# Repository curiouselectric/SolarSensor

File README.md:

# Solar Sensor
A DIY solar irradiance sensor.

Here are the design files (hardware, PCB and firmware) for a relatively low cost solar irradaince sneesor (called a pyranometer).

[Information relating to the design choices for this unit is available in a blog post here](https://www.re-innovation.co.uk/docs/low-cost-diy-solar-irradiance-sensor-for-pv-system-monitoring/).

This pyranometer is design to measure solar irradiance in Watts per meter squared. This is useful for monitoring systems for solar photovoltaic panels. It can also be used as an indicator value for light levels in many systems.

The main things to note with this design are:

* It does not apply any corrections/filtes for human eye parameters (whcih Lux sensors use, typically for photography or dimming algorithms)
* It does not apply any corrections/filters for plant growing characteristics (typically called PAR  - [Photosynthetically active radiation](https://en.wikipedia.org/wiki/Photosynthetically_active_radiation)

The main issue with this design is the calibration of the sensor data to its actual real-world data. I have attempted to give sensible conversion factors for the sensors used, but calibration for each exact set up with 
calibrated measurement equipment is potentially needed, depending upon you application.

If you are looking for relative changes in irradiance then this sensor is perfectly suitable. 

# Overview
This unit reads irradiance from a photo diode sensor (like a P-N junction in a typical solar photovoltaic cell) every 100mS or so. 

The sensor uses an accurate 16 bit Analog to Digital converter (ADC) (rather than the 10 bit resolution on-board the micrcontorller). This allows for much finer montitoring of the very small current from the solar sensor. As the sensor will 'max out' well below typicaly outdoor irradiance levels, then we use a 6mm PTFE diffuse to attenuate the irradiance signal. This was caclualted from trial and error, but allows up to 2000W/m² to be measured.

There is also a temperature sensor on-board to adjust readings for the sensor temperature. 

It averages those values over different sampling periods of 1, 10, 60 (1 min), 600 (10 min), 3600 (1 hour) seconds. It has an ATMega328 microcontroller onboard for measuring the sensors, processing commands and returnign serial data. A simple serial interface has been implemented (at max 57600 baud) to service requests from another device (such as a data logger or monitoring system). The serial requests can also have CRC for error checking.

I originally designed this to interface to an ESP32 data logger, which sleeps most of the time. The ESP32 wakes up, gets the data it needs, then goes back to sleep, knowing the solar sensor is always monitoring.

It was designed as a relatively simple interface to remove the need for monitoring irradiance data and averaging it. 
There are other dvices in this range, [including a wind sensor](https://www.curiouselectric.co.uk/collections/environment/products/wind-sensor-interface).

## Irradiance Measurements

The unit stores average irradiance values from the sensor for 1 second, 10 second, 1 min, 10 min and 1 hour values. It also records the maximum and minimum irradiance.

The unit converts the tiny current from the solar PV cell within a photodiode into a "Watts per meter squared" value using a y=mx+c linear conversion, where y is the irradiance value and x is the ADC reading from the photo diode sensor circuitry. m and c are stored in EEPROM and have default values of m=1 and c=0. These are floats and can be changed as required through the serial interface. Any updated values are stored in EEPROM. The output will not go negative - it will round out at 0.

The photodiode used within the prototype is the [SFH203 from OSRAM](https://look.ams-osram.com/m/67e1a90044b03ee9/original/SFH-203.pdf). This has an output repsonse between 400-1100nm with a sensitive area of 1mm² giving a whopping 80uA of photocurrent!

## Temperature Measurements

Temperature near to the board inside the unit is measured using a surface mounted LM75 I2C temperature sensor. This will give an approximate temperature of the sensor. This sensor is accurate to 0.5C. 
Temperature compensation can be applied by updating the config file within the fireware. If the "APPLY_TEMP_COMP" flag is set to "true" then the "TEMP_COMP_VAL" is applied at the real temperature compare to the "RATED_TEMP". Typically the rated temperature is 25C and comes from the [data sheet](https://look.ams-osram.com/m/67e1a90044b03ee9/original/SFH-203.pdf). For the SFH203 the "TEMP_COMP_VAL" is 0.18 %/K and the "RATED_TEMP" is 25C

So an example would be measuring 500 W/m² but the temperature sensor reads 50C.
The rated temperature is 25C, so we need to apply a compensation of (50 - 25) * 0.18 % = 4.5%, so the sensor will be reading 4.5% under the real value (as output is inversly affected by temperature), So the actual irradiance is 500 + (500*0.045) = 522.5 W/m². Not a huge difference, but this might be important.

You can also remove the temperature compensation and record the irradiance and temperature seperately and apply the compensation later.

# Operation

There are two mode of operation, depending upon your use case:

## Response Mode

In this mode then the unit responds to serial requests made. You ask the sensor for data and this is returned. It never sends anything unless asked. 

## Broadcast Mode

In this mode then the unit regularly sends data via the serial connunication. It will send the averaged data for (0) 1 second, (1) 10 second, (2) 1 min, (3) 10 min and (4) 1 hour averaged data. If this is set to (5) then the unit does not send any data. The send mdoe is stored in EEPROM, so it will start sending data again even if power is lost.

Boradcast mode works well if the logger is always listening and you only have one sensor in range. If more than one sensor is in range then the data will clash and potentially cause issues, in which case use Response mode.

The two modes work together - you can have the unit sending regular data and also responding to requests.

It runs on an ATMega328 running at 8MHz with selectable baud serial (up to 57600). It comes pre-programmed, but code can be uploaded via the Arduino IDE, using the MiniCore board add-on. See firmware for more details.

# Hardware

The PCB was designed in KiCAD and is available here. A small PCB has been designed.
There is one reset switch, one user input switch and one LED output.

## Board ID Number

Each unit can have a unique ID (using a solder pad for 0-7 values), so multiple units can be added to a serial bus, if needed. The defalt is 0.

## PCB User Switch and User LED

There is one user switch and one user LED on the unit.

The LED will show a regular flash every 5 seconds. This will briefly flash once every 5 seconds if the unit is in 'Response' mode. The LED will briefyl flash twice every 5 seconds if the unit is in 'Broadcast' mode. Data will be sent at the broadcast rate.

The LED will also flash whenever data is sent of the serial port. The LED will go on before data sent and then off after data is sent.

Pressing the user switch for >0.5 seconds and then releasing will result in a switch press. 

A switch press will increment the "mode" from 0-1-2-3-4-5 then back to 0. 

The unit will flash after a button press to indicate the broadcast mode (so 0 flashes if the value is 0, 1 flash if the value is 1 etc). 

If this is set to 5 then the unit works in 'Response' mode. 

If this is set to 0-4 then the unit is in 'Broadcast' mode and will send the data at the relevant interval (0 = 1s, 1 = 10s, 2 = 1 min, 3 = 10 min and 4 = 1 hour). 

The mode can also be set with a serial request, using the "Set the unit to broadcast:" method (see below).

# Firmware
This uses an ATMega328 running at 8MHz with 3.3v or 5V supply.

## Initial bootloader installation:
You should not need to do this, as the unit should come with this already installed. This is just for information.

To upload a bootloader it then MiniCore is used:

Install MiniCore from here: https://github.com/MCUdude/MiniCore

Install the bootloader using an Arduino as an ISP. https://www.arduino.cc/en/Tutorial/BuiltInExamples/ArduinoISP

Wire up your arduino and an ISP 3x2 header pin onto the wind sensor PCB.

Choose the "ATMega328" option with the "External 8MHz Oscillator" set.

You can then use the 'Burn Bootloader' option within 'Tools' in the Arduino IDE. This will install the Minicore bootloader.

## Program via Arduino IDE

To program it then MiniCore is used:

Install MiniCore from here: https://github.com/MCUdude/MiniCore

Add to preferences and then board manager.

You can then upload code by choosing the "ATMega328" option with the "External 8MHz Oscillator" set.

# Serial Data and Commands

It returns the average values and information when requested on serial port.

At all other times then the unit is asleep.

This unit is called the Solar Sensor, so I used "SS" as its simple serial name.

## Irradiance data:
REQUEST: “aaI0SSA4#”  ("aaI0SSA4?41#" with CRC)  Where 0 is an ID from 0-7 set by solder on PCB. 4 is the averaging period (0=1s, 1=10s, 2 = 60s, 3 = 600s, 4=3600s)  

RETURNED: "aaI0SSA1:28.5:28.6:28.5:18.0#" 

where the first number (between semi-colons) is the average, 2nd number is the Maximum (until a reset is done), 3rd number is the Minimum and 4th number is the temperature.

Temperature has a resolution of 0.5 C (18.0C in this example).

Response will include the averaging number (1 in this example).
                                      
## Irradiance data minimum:

REQUEST: “aaI0SSMN#” ("aaI0SSMN?dc#" with CRC) - does not matter what averaging period. min/max are just the min/max seen.

RETURNED: "aaI0SSMN:27.9#" where the number after semi-colon is the minimum. (+CRC if requested)
                                      
## Irradiance data maximum:

REQUEST: “aaI0SSMX#”  ("aaI0SSMX?be#" with CRC) - does not matter what averaging period. min/max are just the min/max seen.

RETURNED: "aaI0SSMX:28.9#" where the number after semi-colon is the maximum. (+CRC if requested)

## Reset the min/max:

REQUEST:   “aaI0RESET#” ("aaI0RESET?d9#" with CRC) this will Reset Min & Max.  

RETURNED:  Nothing

This command will reset the min/max. Min and max will be stored until this reset command is issued.

## What is Irradiance Sensor conversion?: 

REQUEST:  "aaI0SSCON#"    Ask for the stored irradiance conversion values

RETURNED: "aaI0SSCONm10.00c0.00#"  With the numbers after m and c being the conversion values (+CRC if requested).
                                      
## Set the Irradiance Sensor conversion:      

REQUEST:  "aaI0SSSETm123.4c567.89#"    SET the stored irradiance conversion values
  
RETURNED: "aaI0SSSETm123.4c567.89#"     With the numbers after m and c being the conversion values

Note: Request: "aaI0SSSETm1c0#" or "aaI0SSSETm1c0?34#" with CRC to set m= 1 and c=0. This is useful for initial testing.

## What is Temperature conversion?: 

REQUEST:  "aaI0SSTCON#"    Ask for the stored conversion values

RETURNED: "aaI0SSTCONp0.18r25.0#"  With the numbers after p being the percentage adjustment and r being the reated temperature (in C) (+CRC if requested).
                                      
## Set the Temperature conversion:      

REQUEST:  "aaI0SSTCONp0.18r25.0#"    SET the stored conversion values
  
RETURNED: "aaI0SSTCONp0.18r25.0#"     With the numbers after m and c being the conversion values

## Switch on/off Temperature conversion: 

REQUEST:  "aaI0SSTCONON#"  to set temperature conversion ON. REQUEST:  "aaI0SSTCONOFF#" to set temperature conversion OFF

RETURNED: "aaI0SSTCONON#" or "aaI0SSTCONOFF#" (+CRC if requested).
                                      
## Set the unit to broadcast:  
REQUEST: "aaI0SEND?#" where ? is an int (0)= 1s data, (1)= 10s data, (2)= 60s/1 min data, (3)= 600s/10 min data, (4)= 3600s/1hr data, (5)= NO data 

RETURNED: "aaI0SENDOK#" + CRC if requested

You can also set the unit to broadcast using the user switch. Press the button for around 0.5s or more then release. This will go through the boradcast modes from 0-1-2-3-4-5 then back round to 0. The LED will flash the number of times for the setting (so send = 0 the unit will not flash, but data will appear within 1 second!).

If the unit is in broadcast mode then the minimum and maximum wind speeds and the wind vane data are all reset each time period.

## What is baud rate?:                 
REQUEST: "aaI0BD#" ("aaI0BD?dc#" with CRC for device ID 0 or "aaI1BD?b7#" for device ID 1)

RETURNED: "aaBD9600#"  // Where 9600 is the baud rate + CRC if requested
                                      
## Set Baud Rate:                      
REQUEST: "aaI0STBD*#"  Where * is (0)1200, (1)2400, (2)9600, (3)57600, (4)115200

RETURNED: "aaBD9600#"   // Where 9600 is the baud rate + CRC if requested

## What is ID?:                        
Mentioned at start up of unit - it is solder-programmed... cannot be changed in code.

ID selection is by using a blob of solder to connect together some pads labelled A0, A1 and A2. The default is for no pads to be soldered and the ID is 0. This means the unit will respond to "I0" as the ID.

To change the ID to another number from 0-7 then we can solder the different connection pads to create a binay number. The connections are:

A0     |A1     |A2     | ID
-------|-------|-------|----
NC     |NC     |NC     | 0
Solder |NC     |NC     | 1
NC     |Solder |NC     | 2
Solder |Solder |NC     | 3
NC     |NC     |Solder | 4
Solder |NC     |Solder | 5
NC     |Solder |Solder | 6
Solder |Solder |Solder | 7

## Serial 'Button' press

The command "aaI0BUTTON" + CRC + "#" will act just like a button press. This is for control via a data logger serial port without access to the physical switch.
e.g. This is "aaI1BUTTON?f4#" including CRC for device ID 1.

## Add CRC check:           
Within the config of the firmware a CRC (Cyclic Redundancy Check) can be added to the data (or not!).

Set this true using the flag in the config.h file:

  #define ADD_CRC_CHECK     true    // Use this to add CRC check to incomming and outgoing messages

This uses the CRC routines from Rob Tillaart, available here: https://github.com/RobTillaart/CRC

A 'crc8' is perfromed on the data and a 2 byte CRC code is added to all replys (and expected on all enquiries). This is added between a ? and # symbol.

If no CRC then the end char is a #.

For example: aaI0RESET?d9# has the CRC check d9 added to the reset request.

Remember: Capitalisation will affect the results: D is not the same as d!

You can use this online calculator to check your CRC: https://crccalc.com/ 

**The type of CRC is CRC-8/SMBUS.**

## Failure codes:

If data is not that length or does not have 'aa' and '#' at start/end then return with send "aaFAIL**#" error code. All will have CRC on these codes, if requested.

## Analog Output

There is an analog output on the device which will always output a voltage which is proportional to the irradiance level. This is useful if you just want to see the data on a multimeter or some panel meter.

The unit is set with a maxinmum irradiance of 2000W/m². This will give the maximum output from the analog output (which will be Vcc (the supply voltage)). At an irradiance of 1000W/m² then the output will be Vcc/2.

This means we need a relatively stable and accurate power supply to give stable and accurate output.

Note: 
* Only have 256 levels for the analog output.
* Need to know Vcc to get absolute value
* Can output up to MAX_IRRADIANCE W/m2 MAX, which is set in the firmware to 2000W/m²
  
Example: So 1000 W/m2 = 256*1000/MAX_IRRADIANCE = PWM Value 128 => Vcc/ 2 (for MAX_IRRADIANCE = 2000 W/m2)
  
Example: So 100 W/m2 = 256*100/MAX_IRRADIANCE = PWM Value 12.8 (or 13 in discrete levels) => Vcc/20 (for MAX_IRRADIANCE = 2000 W/m2)

The resolution of the output is Vcc/256, so for 5V Vcc this is  0.01953V or 19.5mV

A reading of 1000W would be PWM of 128 which gives output of 2.5V

A reading of 100W would should give PWM of 12.8 (so output voltage should be 0.25V) BUT 12.8 is converted to 13 as an INT (rounding up)

So output is actually 0.2539V. Basically there is a 'step' of 19.5mV (at Vcc = 5V) so data will be 'stepped'

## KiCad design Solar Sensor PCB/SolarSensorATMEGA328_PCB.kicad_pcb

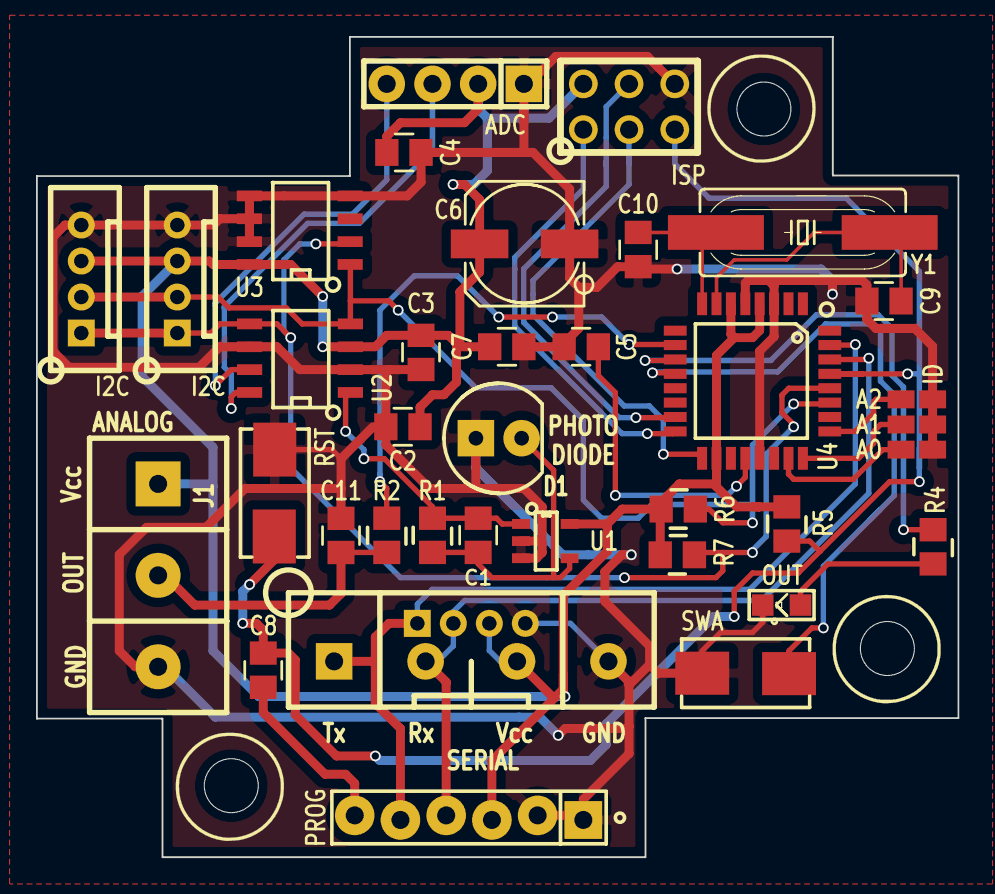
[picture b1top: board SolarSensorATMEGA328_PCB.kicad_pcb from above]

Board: 2 copper layers, 51.2 x 45.6 mm, 36 parts (1 on the bottom side), 26 nets.

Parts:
C1: 10n; SM_C_0805
C2, C3, C4, C5, C7, C8, C11: 100n; SM_C_0805
C6: 100u; SM_6.3x7.7
C9, C10: 22p; SM_C_0805
D1: PHOTO DIODE; LED-5MM_PHOTODIODE
D2: OUT; SM0805_LED
J1: ANALOG; SIL-3_screw_terminal
P1, P10: I2C; SIL-4_Grove_Not_Labelled
P2: SERIAL; SIL-4_Grove_SCREW
P3: ID; SM_6pad_3W_SOLDER
P4: ISP; ISP_3x2
P5: LOGO2; TCEC_Words_13mm
P6: PCB; PCB_SolarSensorATMEGA328_PCB_design_v2
P8: ADC; SIL-4_large_pad
P9: PROG; TH_6x1_FTDI
R1: 47k; SM0805
R2, R5: 10k; SM0805
R4: 470; SM0805
R6, R7: 4k7; SM0805
SW1: SWA; SMD_SW_6x3_5
SW2: RST; SMD_SW_6x3_5
U1: TSV911xxLx; SM_SOT-23-5
U2: MCP3426-xSN; SM_SOIC_8
U3: LM75B; SM_SOIC_8
U4: ATmega328P-AU; TQFP32-08
Y1: 8MHz_XTAL; SM-crystal-HC49UP

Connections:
/ATMega328/A0: P3.5, U4.23
/ATMega328/A1: P3.3, U4.24
/ATMega328/A2: P3.1, U4.25
/ATMega328/D6: R2.1, U4.10
/ATMega328/D7_LED0: R4.1, U4.11
/ATMega328/D8_SWA: SW1.1, U4.12
/ATMega328/DTR: C8.1, P9.6
/ATMega328/MISO: P4.1, U4.16
/ATMega328/MOSI: P4.4, U4.15
/ATMega328/RESET: C8.2, P4.5, R5.2, SW2.1, U4.29
/ATMega328/SCLK: P4.3, U4.17
/I2C_CLK: P1.1, P10.1, R7.2, U2.5, U3.2, U4.28
/I2C_SDA: P1.2, P10.2, R6.2, U2.4, U3.1, U4.27
/IRR_A: C11.1, J1.2, R2.2
/Rx: P2.2, P9.4, U4.30
/Tx: P2.1, P9.5, U4.31
GND: C2.1, C3.2, C4.1, C5.1, C6.2, C7.1, C9.1, C10.1, C11.2, D1.1, D2.1, J1.3, P1.4, P2.4, P3.2, P3.4, P3.6, P4.6, P8.1, P9.1, P9.2, P10.4, SW1.2, SW2.2, U1.2, U1.3, U2.2, U2.6, U3.4, U3.5, U3.6, U3.7, U4.3, U4.5, U4.21
unnamed: C1.1, R1.1, U1.1, U2.1
unnamed: C1.2, D1.2, R1.2, U1.4
unnamed: C5.2, U4.20
unnamed: C9.2, U4.7, Y1.1
unnamed: C10.2, U4.8, Y1.2
unnamed: D2.2, R4.2
unnamed: P8.3, U2.8
unnamed: P8.4, U2.7
VCC: C2.2, C3.1, C4.2, C6.1, C7.2, J1.1, P1.3, P2.3, P4.2, P8.2, P9.3, P10.3, R5.1, R6.1, R7.1, U1.5, U2.3, U3.8, U4.4, U4.6, U4.18

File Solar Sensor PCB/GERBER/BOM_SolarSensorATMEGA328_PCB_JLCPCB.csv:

Comment,Designator,Footprint,LCSC
"10n","C1","REInnovationFootprint:SM_C_0805","C107135"
"22p","C9,C10","REInnovationFootprint:SM_C_0805","C1804"
"100n","C2,C3,C4,C5,C7,C8,C11","REInnovationFootprint:SM_C_0805","C49678"
"100u","C6","REInnovationFootprint:SM_6.3x7.7","C164071"
"PHOTO DIODE","D1","REInnovationFootprint:LED-5MM_PHOTODIODE",""
"OUT","D2","REInnovationFootprint:SM0805_LED","C2296"
"ANALOG","J1","REInnovationFootprint:SIL-3_screw_terminal",""
"I2C","P1,P10","REInnovationFootprint:SIL-4_Grove_Not_Labelled",""
"SERIAL","P2","REInnovationFootprint:SIL-4_Grove_SCREW",""
"ID","P3","REInnovationFootprint:SM_6pad_3W_SOLDER",""
"ISP","P4","REInnovationFootprint:ISP_3x2",""
"LOGO2","P5","CuriousElectric3:TCEC_Words_13mm",""
"PCB","P6","REInnovationFootprint:PCB_SolarSensorATMEGA328_PCB_design_v2",""
"ENC","P7","",""
"ADC","P8","REInnovationFootprint:SIL-4_large_pad",""
"PROG","P9","REInnovationFootprint:TH_6x1_FTDI",""
"47k","R1","REInnovationFootprint:SM0805","C17713"
"10k","R2,R5","REInnovationFootprint:SM0805","C17414"
"470","R4","REInnovationFootprint:SM0805","C17710"
"4k7","R6,R7","REInnovationFootprint:SM0805","C17673"
"SWA","SW1","REInnovationFootprint:SMD_SW_6x3_5","C412368"
"RST","SW2","REInnovationFootprint:SMD_SW_6x3_5","C412368"
"TSV911xxLx","U1","REInnovationFootprint:SM_SOT-23-5","C361052"
"MCP3426-xSN","U2","REInnovationFootprint:SM_SOIC_8",""
"LM75B","U3","REInnovationFootprint:SM_SOIC_8","C34565"
"ATmega328P-AU","U4","REInnovationFootprint:TQFP32-08","C14877"
"8MHz_XTAL","Y1","REInnovationFootprint:SM-crystal-HC49UP","C12674"

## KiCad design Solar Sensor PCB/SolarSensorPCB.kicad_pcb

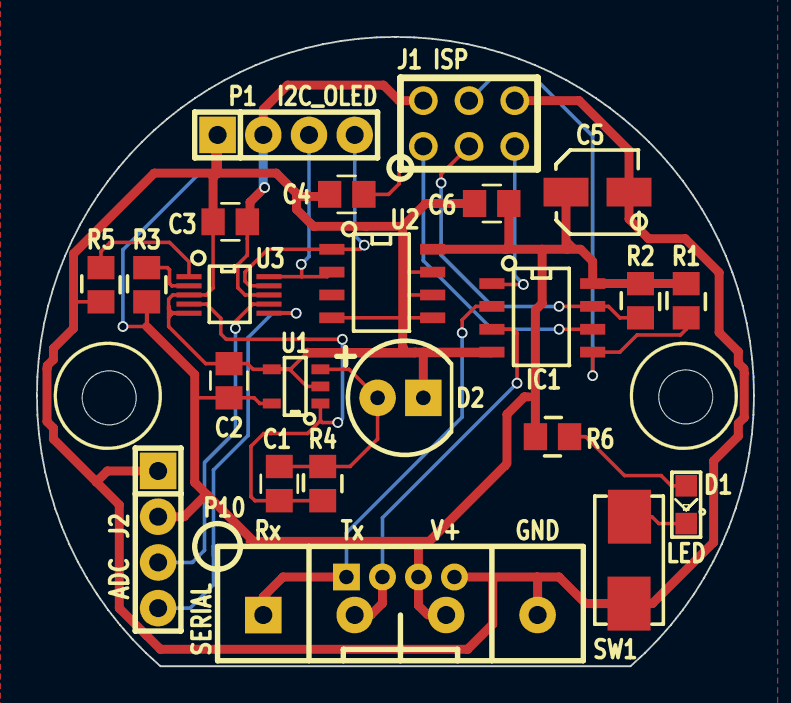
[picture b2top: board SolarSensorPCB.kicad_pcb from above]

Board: 2 copper layers, 39.8 x 35.0 mm, 25 parts (1 on the bottom side), 18 nets.

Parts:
C1: 10n; SM_C_0805
C2, C3, C4, C6: 100n; SM_C_0805
C5: 100u; SM_4x5.3
D1: LED; SM0805_LED
D2: PHOTO DIODE; TH_LED-5MM_larg_pad
IC1: ATTINY85-P; SM_SOIC_8
J1: ISP; ISP_3x2
J2: ADC; SIL-4_large_pad
P1: I2C_OLED; SIL-4_large_pad
P5: LOGO2; TCEC_Words_13mm
P6: PCB; PCB_40mm_Round_SolarSensorPCB_design
P10: SERIAL; SIL-4_Grove_SCREW
R1, R2, R3, R5: 10k; SM0805
R4: 47k; SM0805
R6: 330R; SM0805
SW1: UP; SMD_SW_6x3_5
U1: TSV911xxLx; SM_SOT-23-5
U2: LM75B; SM_SOIC_8
U3: ADS1115; SM_MSOP10-0.5

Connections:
+5V: C2.2, C3.1, C4.2, C5.1, C6.1, IC1.8, J1.2, J2.2, P1.2, P10.3, R1.1, R2.1, R3.1, R6.1, U1.5, U2.8, U3.8
/D0: IC1.5, J1.4, R1.2
/D1: IC1.6, J1.1
/D2: IC1.7, J1.3, R2.2
/D3: IC1.2, P10.1
/D4: IC1.3, P10.2
/SCL_I2C: P1.3, U2.2, U3.10
/SDA_I2C: P1.4, U2.1, U3.9
/SW1: D1.1, SW1.1
GND: C2.1, C3.2, C4.1, C5.2, C6.2, D2.2, IC1.4, J1.6, J2.1, P1.1, P10.4, R5.1, SW1.2, U1.2, U1.4, U2.4, U2.5, U2.6, U2.7, U3.3, U3.5
unnamed: C1.1, R4.1, U1.1, U3.4
unnamed: C1.2, D2.1, R4.2, U1.3
unnamed: D1.2, R6.2
unnamed: IC1.1, J1.5
unnamed: J2.3, U3.7
unnamed: J2.4, U3.6
unnamed: R3.2, U3.2
unnamed: R5.2, U3.1

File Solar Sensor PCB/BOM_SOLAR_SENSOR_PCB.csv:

Reference, Value, Footprint, Datasheet, JLCPCB Add, JLCPCB Cost, LCSC, Description, Manufacturer, Manufacturer Part No, Notes, Supplier 1, Supplier 1 Cost, Supplier 1 Part No, Supplier 2, Supplier 2 Cost, Supplier 2 Part No
P10,SERIAL,REInnovationFootprint:SIL-4_Grove_SCREW,,,,,,,,,,,,,,
SW1,UP,REInnovationFootprint:SMD_SW_6x3_5,,Y,0.0391,C319333,,,,,,,,,,
R4,47k,REInnovationFootprint:SM0805,,Y,0.004,C17713,,,,,,,,,,
D2,PHOTO DIODE,REInnovationFootprint:TH_LED-5MM_larg_pad,,,,,~,~,~,~,~,~,~,~,~,~
C1,10n,REInnovationFootprint:SM_C_0805,,Y,0.0105,C107135,,,,,,,,,,
P5,LOGO2,CuriousElectric3:TCEC_Words_13mm,,,,,,,,,,,,,,
P6,PCB,REInnovationFootprint:PCB_40mm_Round,,,,,,,,,,,,,,
P7,ENC,,https://www.rapidonline.com/pdf/30-3800e.pdf,,,,~,~,~,~,Rapid,4.37,30-3804,~,~,~
C5,100u,REInnovationFootprint:SM_4x5.3,,Y,0.0566,C134722,,,,,,,,,,
C6,100n,REInnovationFootprint:SM_C_0805,,Y,0.0108,C49678,,,,,,,,,,
U3,ADS1115,REInnovationFootprint:SM_MSOP10-0.5,,Y,4.7766,C37593,,,,,,,,,,
R3,10k,REInnovationFootprint:SM0805,~,Y,0.004,C17414,,,,,,,,,,
C3,100n,REInnovationFootprint:SM_C_0805,,Y,0.0108,C49678,,,,,,,,,,
R1,10k,REInnovationFootprint:SM0805,~,Y,0.0045,C38522,,,,,,,,,,
R2,10k,REInnovationFootprint:SM0805,~,Y,0.0045,C17414,,,,,,,,,,
R5,10k,REInnovationFootprint:SM0805,~,Y,0.004,C38522,,,,,,,,,,
C2,100n,REInnovationFootprint:SM_C_0805,,Y,0.0108,C49678,,,,,,,,,,
IC1,ATTINY85-P,REInnovationFootprint:SM_SOIC_8,,,,,,,,,,,,,,
J1,ISP,REInnovationFootprint:ISP_3x2,~,,,,,,,,,,,,,
R6,330R,REInnovationFootprint:SM0805,~,Y,0.005,C237764,,,,,,,,,,
D1,LED,REInnovationFootprint:SM0805_LED,~,Y,0.0135,C2293,,,,,,,,,,
U1,TSV911xxLx,REInnovationFootprint:SM_SOT-23-5,www.st.com/resource/en/datasheet/tsv911.pdf,Y,0.4576,C361052,,,,,,,,,,
J2,ADC,REInnovationFootprint:SIL-4_large_pad,~,,,,,,,,,,,,,
U2,LM75B,REInnovationFootprint:SM_SOIC_8,http://www.ti.com/lit/ds/symlink/lm75b.pdf,Y,0.3457,C34565,,,,,,,,,,
C4,100n,REInnovationFootprint:SM_C_0805,,Y,0.0108,C49678,,,,,,,,,,
P1,I2C_OLED,REInnovationFootprint:SIL-4_large_pad,,,,,,,,,,,,,,
,,,,,,,,,,,,,,,,
,,,,COST,5.7688,,,,,,,,,,,

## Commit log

2017-06-11 Initial commit of files
2021-06-20 Large update of firmware and PCB
2021-06-20 Updated PCB. Not finished yet!
2021-07-04 Updated PCB v0.1
2021-07-16 Updated firmware. Updated PCB
2021-07-19 big update of PCB
    Changed from ATTiny85 to ATmega328
2021-10-29 large update of firmware & PCB changes
    This version works
2021-11-28 Updated diffuser design
2021-12-05 Updated diffuser model
2021-12-05 PCB update small
2021-12-17 updated new PCB version
2022-01-01 Updated PCB and Firmware
    Added 3D models to new Kicad PCB
2022-04-05 Updated firmware.
    Sorted serial requests
2022-04-14 Updated Firmware. Updated Mounting design
    Firmware not fully complete - still needs temperature compensation.
2022-04-14 Firmware update- added temperature compensation
2025-03-10 Large update
    Add CRC to firmware
    Update readme
    Update PCB to kicad 9
2025-03-10 updated images
2025-03-10 delet images
2025-03-10 updated temp compensation calculation
2025-03-12 updated with temperature compensation updating
